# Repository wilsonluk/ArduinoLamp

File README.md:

Arduino Lamp
============
This Arduinio software and PCB are used to control an LED Desk Lamp.

Repository Contents (Needs Cleanup)
-----------------------------------
* **/Code**  - Arduino Code for LED brightness and color control, temperature monitor, and fan control
* **/Mounting**  - 3D Printer Models for mounting hardware
* **/Hardware**  - PCB Files and Parts Lists

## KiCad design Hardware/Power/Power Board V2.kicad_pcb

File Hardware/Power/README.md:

Arduino Lamp - Hardware
============
Hardaware Files (PCB Design, Component Choice / BOM).<br>
PCB / Schematic created using *[KiCad](https://kicad-pcb.org/)*

Folder Contents
---------
* **/BOM**  - Bill of Materials
* **/Datasheets**  - Datasheets for Major Hardaware Components (PMICs, HSF, LEDs)
* **/Libraries**  - KiCad Library Files for Symbols and Footprints
* **/PCB**  - KiCad PCB Files
* **/Resources**  - Other Resources
* **/Schematic**  - KiCad Schematic Files

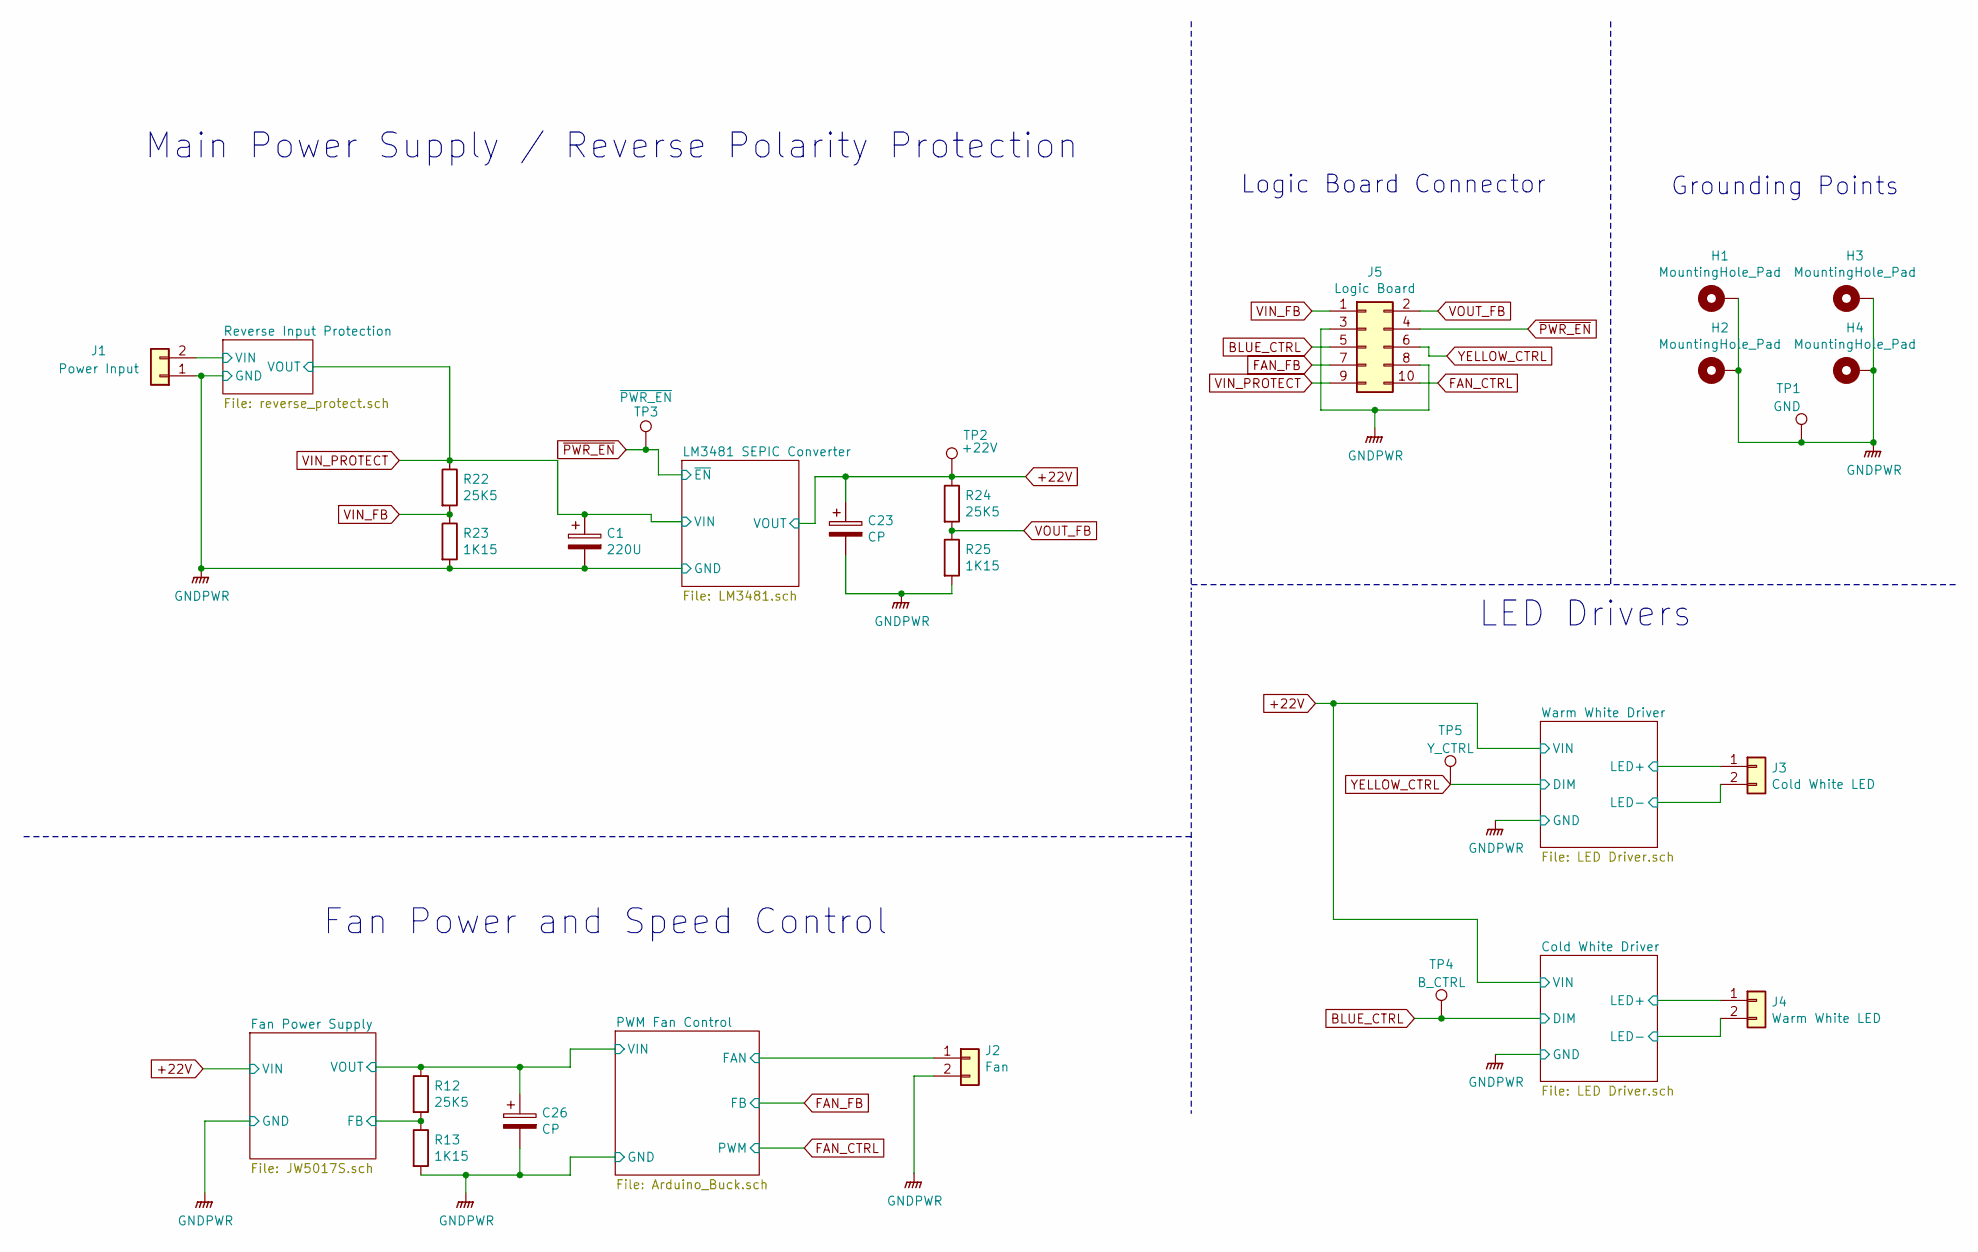
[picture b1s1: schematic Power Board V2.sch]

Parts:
C1: 220U; CP_Radial_D8.0mm_P3.50mm
C23: CP; CP_Radial_D10.0mm_P5.00mm
C26: CP; CP_Radial_D6.3mm_P2.50mm
H1, H2, H3, H4: MountingHole_Pad; MountingHole_3.2mm_M3_Pad_Via
J1: Power Input; JST_XH_B2B-XH-A_1x02_P2.50mm_Vertical
J2: Fan; JST_XH_B2B-XH-A_1x02_P2.50mm_Vertical
J3: Cold White LED; JST_XH_B2B-XH-A_1x02_P2.50mm_Vertical
J4: Warm White LED; JST_XH_B2B-XH-A_1x02_P2.50mm_Vertical
J5: Logic Board; IDC-Header_2x05_P2.54mm_Vertical
R12, R22, R24: 25K5; R_0603_1608Metric_Pad1.05x0.95mm_HandSolder; Manufacturer_Part_Number RS-05K2552FT
R13, R23, R25: 1K15; R_0603_1608Metric_Pad1.05x0.95mm_HandSolder; Manufacturer_Part_Number RS-03K1151FT
TP1: GND; TestPoint_Pad_D1.5mm
TP2: +22V; TestPoint_Pad_D1.5mm
TP3: ~PWR_EN; TestPoint_Pad_D1.5mm
TP4: B_CTRL; TestPoint_Pad_D1.5mm
TP5: Y_CTRL; TestPoint_Pad_D1.5mm

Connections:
+22V: C23.1, R24.1, TP2.1; also elsewhere on the board
/Cold White Driver/LED+: J4.1; also elsewhere on the board
/Cold White Driver/LED-: J4.2; also elsewhere on the board
/Fan Power Supply/FB: R12.2, R13.1; also elsewhere on the board
/PWM Fan Control/FAN: J2.1; also elsewhere on the board
/PWM Fan Control/VIN: C26.1, R12.1; also elsewhere on the board
/Reverse Input Protection/VIN: J1.2; also elsewhere on the board
/Warm White Driver/LED+: J3.1; also elsewhere on the board
/Warm White Driver/LED-: J3.2; also elsewhere on the board
BLUE_CTRL: J5.5, TP4.1; also elsewhere on the board
FAN_CTRL: J5.10; also elsewhere on the board
FAN_FB: J5.7; also elsewhere on the board
GNDPWR: C1.2, C23.2, C26.2, H1.1, H2.1, H3.1, H4.1, J1.1, J2.2, J5.3, J5.8, R13.2, R23.2, R25.2, TP1.1; also elsewhere on the board
VIN_FB: J5.1, R22.2, R23.1
VIN_PROTECT: C1.1, J5.9, R22.1; also elsewhere on the board
VOUT_FB: J5.2, R24.2, R25.1
YELLOW_CTRL: J5.6, TP5.1; also elsewhere on the board
~PWR_EN: J5.4, TP3.1; also elsewhere on the board

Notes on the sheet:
LED Drivers
Grounding Points
Logic Board Connector
Fan Power and Speed Control
Main Power Supply / Reverse Polarity Protection

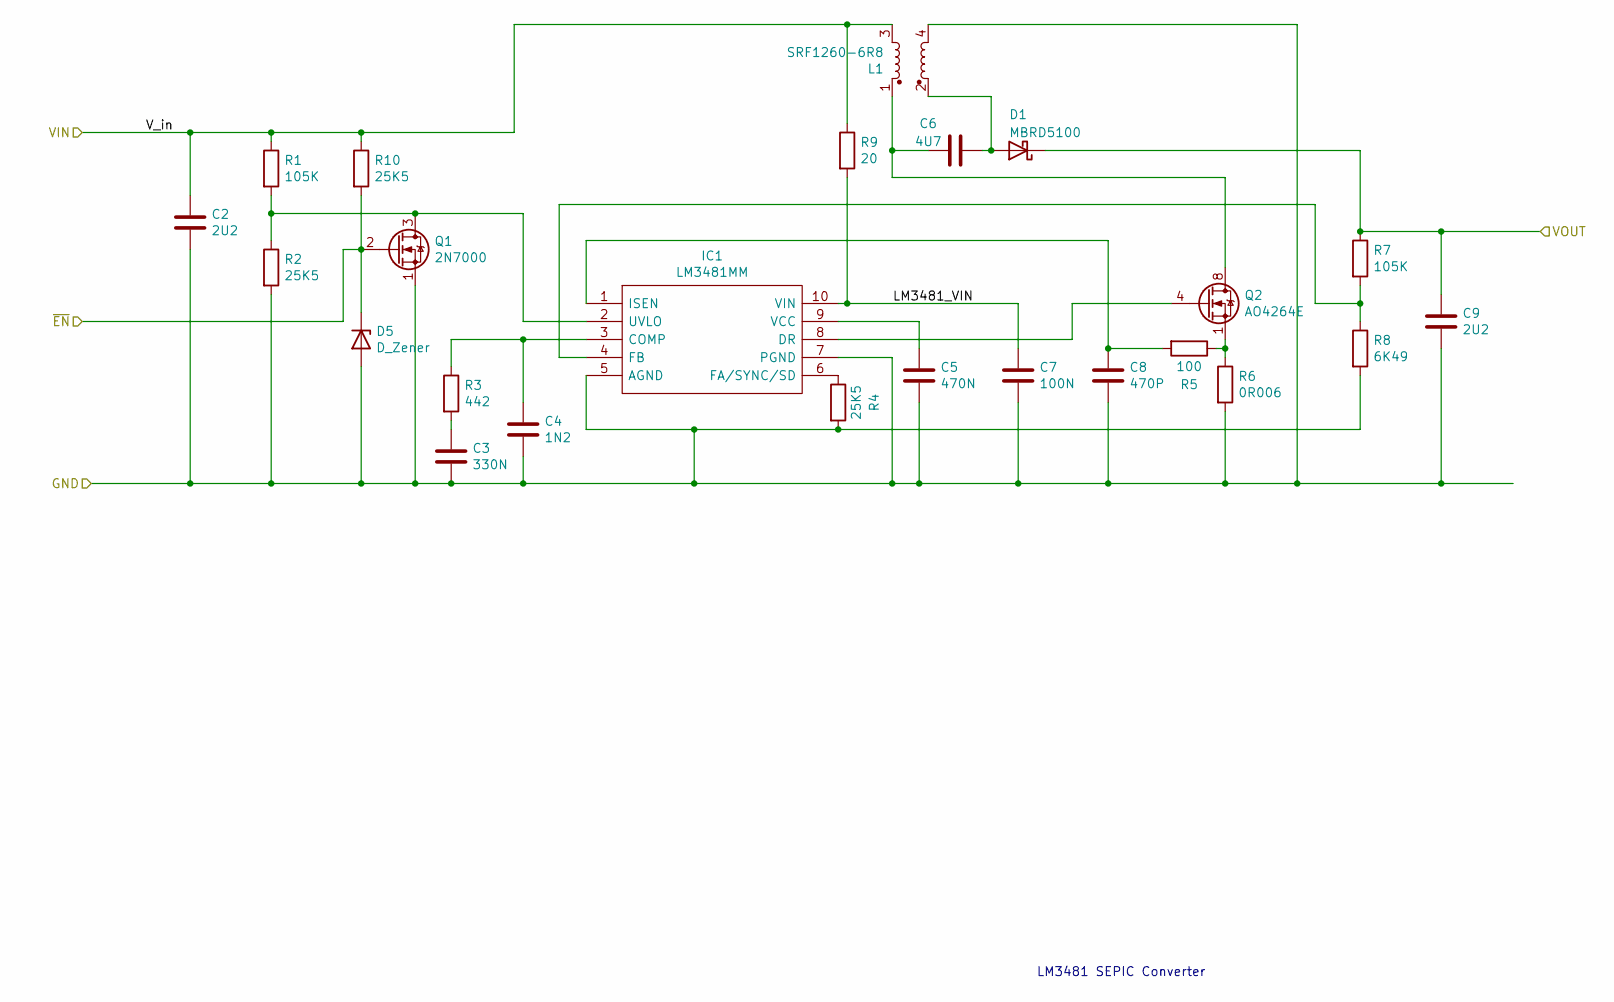
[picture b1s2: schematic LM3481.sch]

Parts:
C2, C9: 2U2; C_0805_2012Metric_Pad1.15x1.40mm_HandSolder; Manufacturer_Part_Number C0805X5R225K500NT
C3: 330N; C_0603_1608Metric_Pad1.05x0.95mm_HandSolder; Manufacturer_Part_Number TCC0603X7R334K500CT
C4: 1N2; C_0603_1608Metric_Pad1.05x0.95mm_HandSolder; Manufacturer_Part_Number C1608C0G1H122JT000N
C5: 470N; C_0603_1608Metric_Pad1.05x0.95mm_HandSolder; Manufacturer_Part_Number 0603B474K100CT
C6: 4U7; C_1206_3216Metric_Pad1.42x1.75mm_HandSolder; Manufacturer_Part_Number GRM31CR71H475KA12L
C7: 100N; C_0603_1608Metric_Pad1.05x0.95mm_HandSolder; Manufacturer_Part_Number CL10B104KB8NNNC
C8: 470P; C_0603_1608Metric_Pad1.05x0.95mm_HandSolder; Manufacturer_Part_Number TCC0603COG471J500CT
D1: MBRD5100; TO-252-2_ConnectedPins
D5: D_Zener; D_SOD-323_HandSoldering; Mouser Part Number MM3Z4V7ST1G
IC1: LM3481MM; VSSOP-10_3x3mm_P0.5mm; Mouser Part Number LM3481MM
L1: SRF1260-6R8; L_Bourns_SRF1260_HandSoldering; Mouser Part Number SRF1260-6R8
Q1: 2N7000; TO-92_Inline; Manufacturer_Part_Number 2N7000
Q2: AO4264E; SO-8_3.9x4.9mm_P1.27mm; Manufacturer_Part_Number AO4264E
R1, R7: 105K; R_0603_1608Metric_Pad1.05x0.95mm_HandSolder; Manufacturer_Part_Number RC0603FR-07105KL
R2, R4, R10: 25K5; R_0603_1608Metric_Pad1.05x0.95mm_HandSolder; Manufacturer_Part_Number RS-05K2552FT
R3: 442; R_0603_1608Metric_Pad1.05x0.95mm_HandSolder; Manufacturer_Part_Number 0603WAF4420T5E
R5: 100; R_0603_1608Metric_Pad1.05x0.95mm_HandSolder; Manufacturer_Part_Number 0603WAJ0101T5E
R6: 0R006; R_1206_3216Metric_Pad1.42x1.75mm_HandSolder; Manufacturer_Part_Number PA1206FRF070R006L
R8: 6K49; R_0603_1608Metric_Pad1.05x0.95mm_HandSolder; Manufacturer_Part_Number RS-03K6491FT
R9: 20; R_0603_1608Metric_Pad1.05x0.95mm_HandSolder; Manufacturer_Part_Number RS-03K19R6FT

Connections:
+22V: C9.1, D1.1 (K), R7.1; also elsewhere on the board
/LM3481 SEPIC Converter/LM3481_VIN: C7.1, IC1.10 (VIN), R9.2
GNDPWR: C2.2, C3.2, C4.2, C5.2, C7.2, C8.2, C9.2, D5.2 (A), IC1.5 (AGND), IC1.7 (PGND), L1.4, Q1.1 (S), R2.2, R4.2, R6.2, R8.2; also elsewhere on the board
unnamed: C3.1, R3.2
unnamed: C4.1, IC1.3 (COMP), R3.1
unnamed: C5.1, IC1.9 (VCC)
unnamed: C6.1, L1.1, Q2.5 (D), Q2.6 (D), Q2.7 (D), Q2.8 (D)
unnamed: C6.2, D1.2 (A), L1.2
unnamed: C8.1, IC1.1 (ISEN), R5.2
unnamed: IC1.2 (UVLO), Q1.3 (D), R1.2, R2.1
unnamed: IC1.4 (FB), R7.2, R8.1
unnamed: IC1.6 (FA/SYNC/SD), R4.1
unnamed: IC1.8 (DR), Q2.4 (G)
unnamed: Q2.1 (S), Q2.2 (S), Q2.3 (S), R5.1, R6.1
VIN_PROTECT: C2.1, L1.3, R1.1, R9.1, R10.1; also elsewhere on the board
~PWR_EN: D5.1 (K), Q1.2 (G), R10.2; also elsewhere on the board

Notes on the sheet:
LM3481 SEPIC Converter

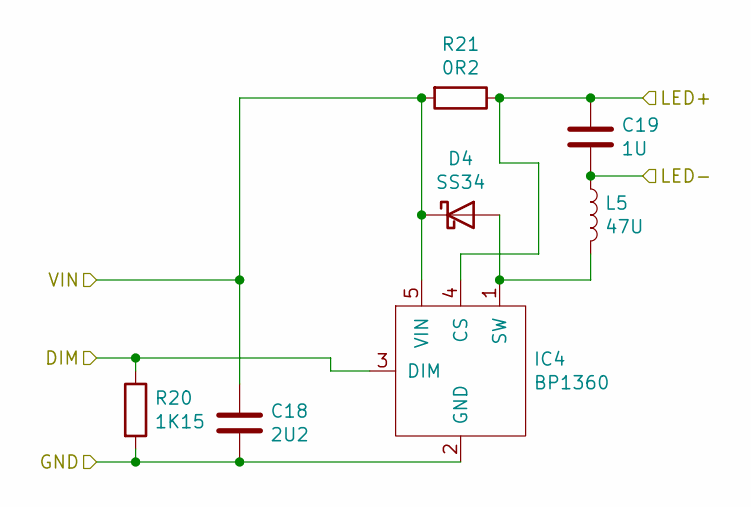
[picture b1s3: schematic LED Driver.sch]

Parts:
C15: 2U2; C_0805_2012Metric_Pad1.15x1.40mm_HandSolder; Manufacturer_Part_Number C0805X5R225K500NT
C16: 1U; C_0805_2012Metric_Pad1.15x1.40mm_HandSolder; Manufacturer_Part_Number TCC0805X7R105K500DTS
D2: SS34; D_SMC_Handsoldering_Shortened
IC2: BP1360; SOT-23-5_HandSoldering; Manufacturer_Part_Number BP1360
L3: 47U; SLD10; Manufacturer_Part_Number SLD10D50S470MTT
R14: 1K15; R_0603_1608Metric_Pad1.05x0.95mm_HandSolder; Manufacturer_Part_Number RS-03K1151FT
R15: 0R2; R_1206_3216Metric_Pad1.42x1.75mm_HandSolder; Manufacturer_Part_Number 1206W3J020LT5E

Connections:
+22V: C15.1, D2.1 (K), IC2.5 (VIN), R15.2; also elsewhere on the board
/Warm White Driver/LED+: C16.1, IC2.4 (CS), R15.1; also elsewhere on the board
/Warm White Driver/LED-: C16.2, L3.1; also elsewhere on the board
GNDPWR: C15.2, IC2.2 (GND), R14.2; also elsewhere on the board
unnamed: D2.2 (A), IC2.1 (SW), L3.2
YELLOW_CTRL: IC2.3 (DIM), R14.1; also elsewhere on the board

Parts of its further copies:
C18: 2U2; C_0805_2012Metric_Pad1.15x1.40mm_HandSolder; Manufacturer_Part_Number C0805X5R225K500NT
C19: 1U; C_0805_2012Metric_Pad1.15x1.40mm_HandSolder; Manufacturer_Part_Number TCC0805X7R105K500DTS
D4: SS34; D_SMC_Handsoldering_Shortened
IC4: BP1360; SOT-23-5_HandSoldering; Manufacturer_Part_Number BP1360
L5: 47U; SLD10; Manufacturer_Part_Number SLD10D50S470MTT
R20: 1K15; R_0603_1608Metric_Pad1.05x0.95mm_HandSolder; Manufacturer_Part_Number RS-03K1151FT
R21: 0R2; R_1206_3216Metric_Pad1.42x1.75mm_HandSolder; Manufacturer_Part_Number 1206W3J020LT5E

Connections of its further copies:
+22V: C18.1, D4.1 (K), IC4.5 (VIN), R21.2; also elsewhere on the board
/Cold White Driver/LED+: C19.1, IC4.4 (CS), R21.1; also elsewhere on the board
/Cold White Driver/LED-: C19.2, L5.1; also elsewhere on the board
BLUE_CTRL: IC4.3 (DIM), R20.1; also elsewhere on the board
GNDPWR: C18.2, IC4.2 (GND), R20.2; also elsewhere on the board
unnamed: D4.2 (A), IC4.1 (SW), L5.2

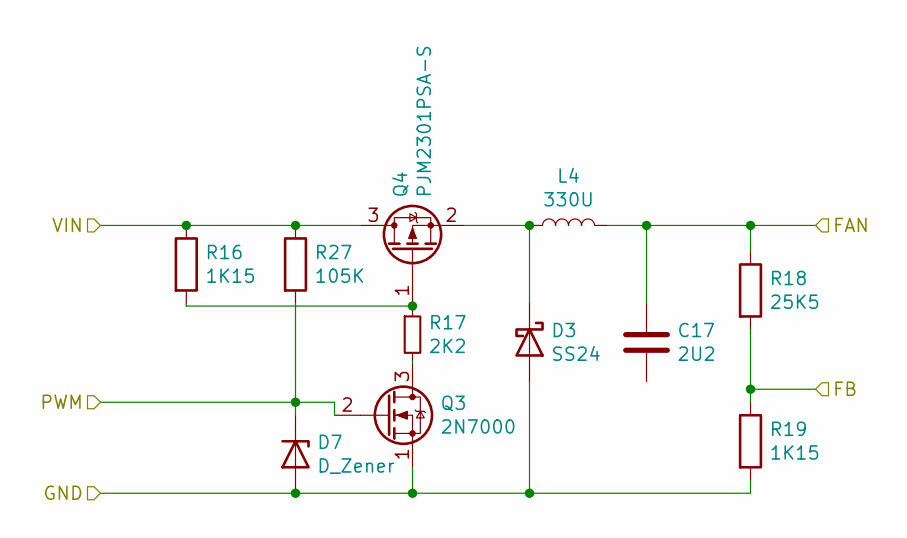
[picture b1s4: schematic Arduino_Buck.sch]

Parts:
C17: 2U2; C_0805_2012Metric_Pad1.15x1.40mm_HandSolder; Manufacturer_Part_Number C0805X5R225K500NT
D3: SS24; D_SMA_Handsoldering_Shortened
D7: D_Zener; D_SOD-323_HandSoldering
L4: 330U; SLD10; Manufacturer_Part_Number SLD10D40S331MTT
Q3: 2N7000; TO-92_Inline; Manufacturer_Part_Number 2N7000
Q4: PJM2301PSA-S; SOT-23; Manufacturer_Part_Number PJM2301PSA-S
R16: 1K15; R_0603_1608Metric_Pad1.05x0.95mm_HandSolder
R17: 2K2; R_0603_1608Metric_Pad1.05x0.95mm_HandSolder
R18: 25K5; R_0603_1608Metric_Pad1.05x0.95mm_HandSolder; Manufacturer_Part_Number RS-05K2552FT
R19: 1K15; R_0603_1608Metric_Pad1.05x0.95mm_HandSolder; Manufacturer_Part_Number RS-03K1151FT
R27: 105K; R_0603_1608Metric_Pad1.05x0.95mm_HandSolder; Manufacturer_Part_Number RC0603FR-07105KL

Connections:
/PWM Fan Control/FAN: C17.1, L4.2, R18.1; also elsewhere on the board
/PWM Fan Control/VIN: Q4.3 (D), R16.1, R27.1; also elsewhere on the board
FAN_CTRL: D7.1 (K), Q3.2 (G), R27.2; also elsewhere on the board
FAN_FB: R18.2, R19.1; also elsewhere on the board
GNDPWR: D3.2 (A), D7.2 (A), Q3.1 (S), R19.2; also elsewhere on the board
unnamed: D3.1 (K), L4.1, Q4.2 (S)
unnamed: Q3.3 (D), R17.2
unnamed: Q4.1 (G), R16.2, R17.1

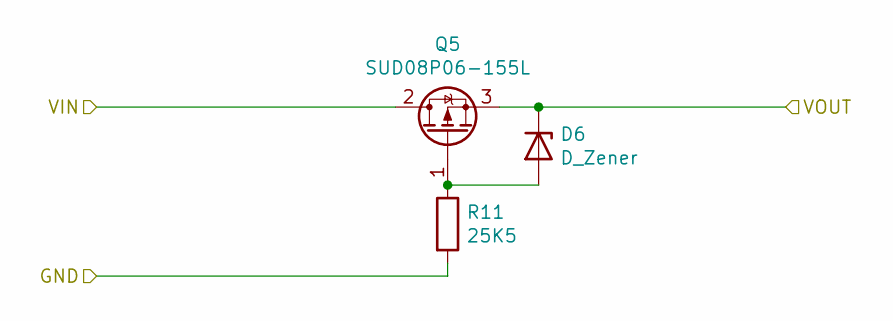
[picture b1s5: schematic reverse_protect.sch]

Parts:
D6: D_Zener; D_SOD-323_HandSoldering
Q5: SUD08P06-155L; TO-252-2
R11: 25K5; R_0603_1608Metric_Pad1.05x0.95mm_HandSolder; Manufacturer_Part_Number RS-05K2552FT

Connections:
/Reverse Input Protection/VIN: Q5.2 (D); also elsewhere on the board
GNDPWR: R11.2; also elsewhere on the board
unnamed: D6.2 (A), Q5.1 (G), R11.1
VIN_PROTECT: D6.1 (K), Q5.3 (S); also elsewhere on the board

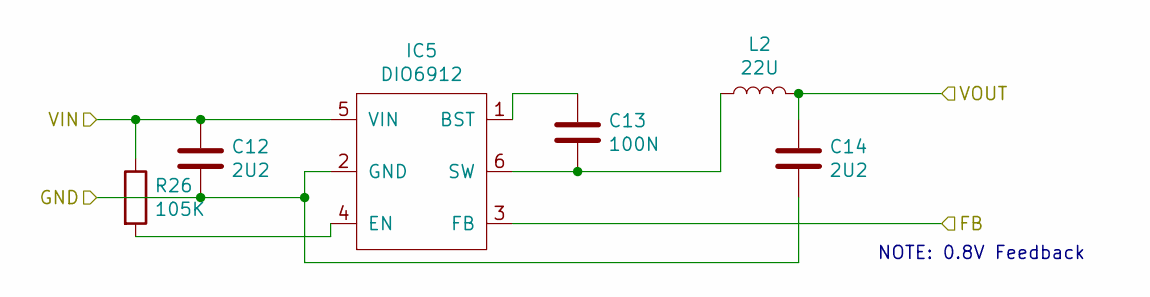
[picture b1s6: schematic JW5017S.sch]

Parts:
C20, C22: 2U2; C_0805_2012Metric_Pad1.15x1.40mm_HandSolder; Manufacturer_Part_Number C0805X5R225K500NT
C21: 100N; C_0603_1608Metric_Pad1.05x0.95mm_HandSolder; Manufacturer_Part_Number CL10B104KB8NNNC
IC3: DIO6912; SOT-23-6_Handsoldering; Manufacturer_Part_Number DIO6912
L6: 22U; YT0630; Manufacturer_Part_Number YT0630-220M
R26: 105K; R_0603_1608Metric_Pad1.05x0.95mm_HandSolder; Manufacturer_Part_Number RC0603FR-07105KL

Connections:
+22V: R26.1; also elsewhere on the board
unnamed 31: R26.2; also elsewhere on the board

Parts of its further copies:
C12, C14: 2U2; C_0805_2012Metric_Pad1.15x1.40mm_HandSolder; Manufacturer_Part_Number C0805X5R225K500NT
C13: 100N; C_0603_1608Metric_Pad1.05x0.95mm_HandSolder; Manufacturer_Part_Number CL10B104KB8NNNC
IC5: DIO6912; SOT-23-6_Handsoldering; Manufacturer_Part_Number DIO6912
L2: 22U; YT0630; Manufacturer_Part_Number YT0630-220M

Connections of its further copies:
+22V: C12.1, IC5.5 (VIN); also elsewhere on the board
/Fan Power Supply/FB: IC5.3 (FB); also elsewhere on the board
/PWM Fan Control/VIN: C14.1, L2.2; also elsewhere on the board
GNDPWR: C12.2, C14.2, IC5.2 (GND); also elsewhere on the board
unnamed: C13.1, IC5.1 (BST)
unnamed: C13.2, IC5.6 (SW), L2.1
unnamed 31: IC5.4 (EN); also elsewhere on the board

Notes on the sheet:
NOTE: 0.8V Feedback

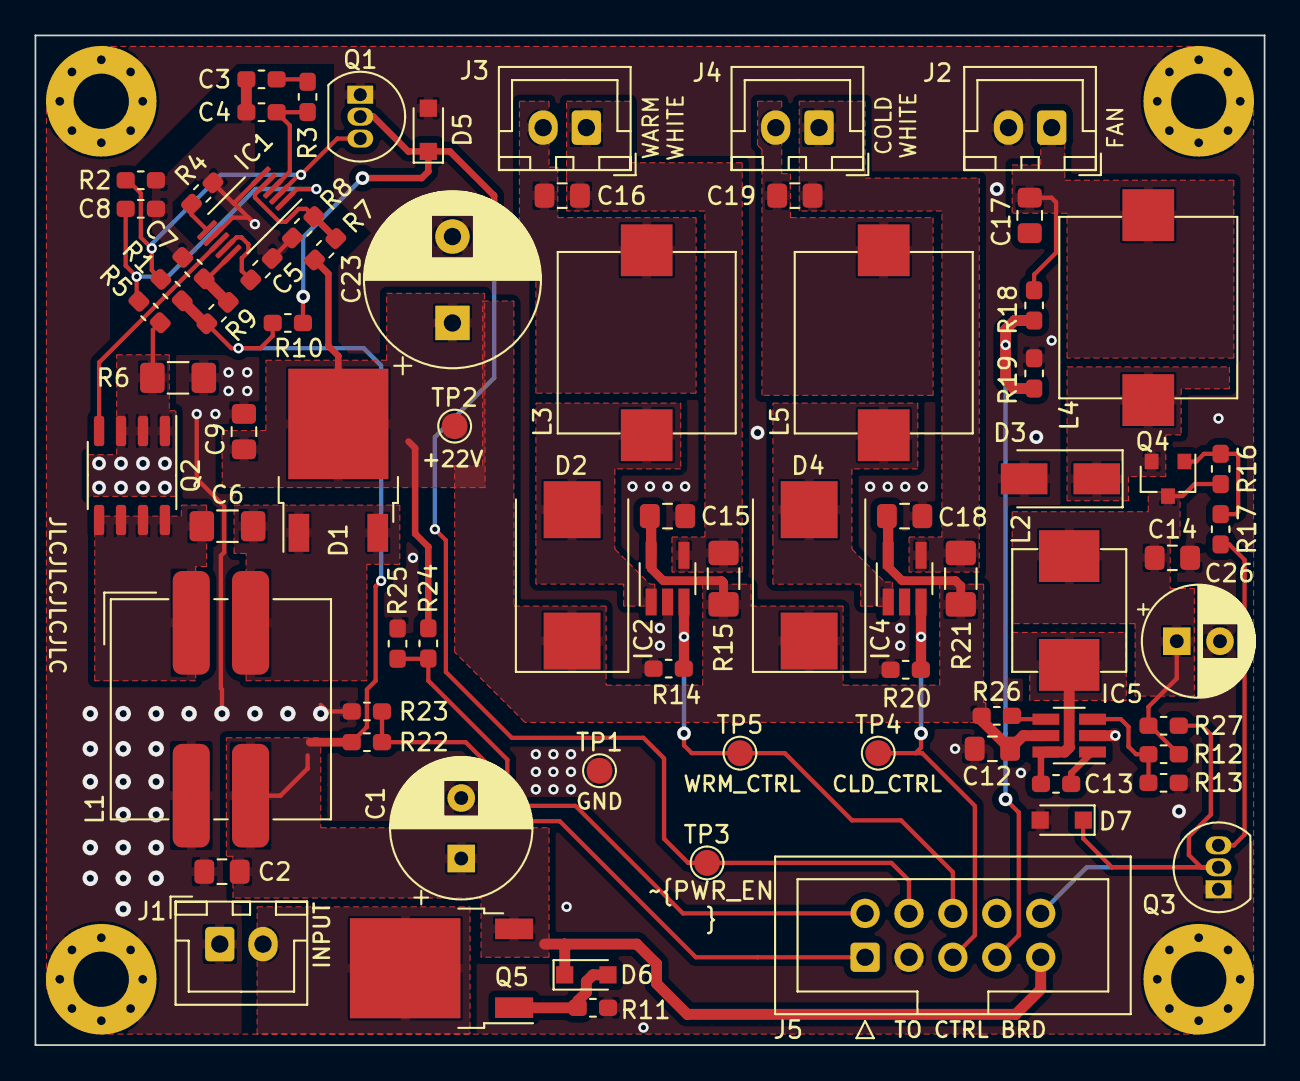
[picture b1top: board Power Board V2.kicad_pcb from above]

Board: 2 copper layers, 71.1 x 58.4 mm, 81 parts (0 on the bottom side), 39 nets.

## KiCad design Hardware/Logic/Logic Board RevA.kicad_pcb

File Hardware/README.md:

Arduino Lamp Hardware
=====================
PCB Files and Libraries for the ArduinoLamp

Lastest PCB revisions created using *[KiCad](https://kicad-pcb.org/)*.

Power Board V1 created using *[EAGLE](https://www.autodesk.com/products/eagle/overview/)* (see ZIP archive).

Folder Contents
-----------------------------------
* **/BOM**  - Bill of Materials of the PCBs
* **/Datasheets**  - Datasheets for relevant ICs and other components
* **/Libraries**  - KiCad Footprint and Schematic Libraries
* **/Logic** - KiCad schematic and layout files for Logic Board
* **/Power** - KiCad schematic and layout files for Power Board
* **/Resources** - Misc. Resources for Boards

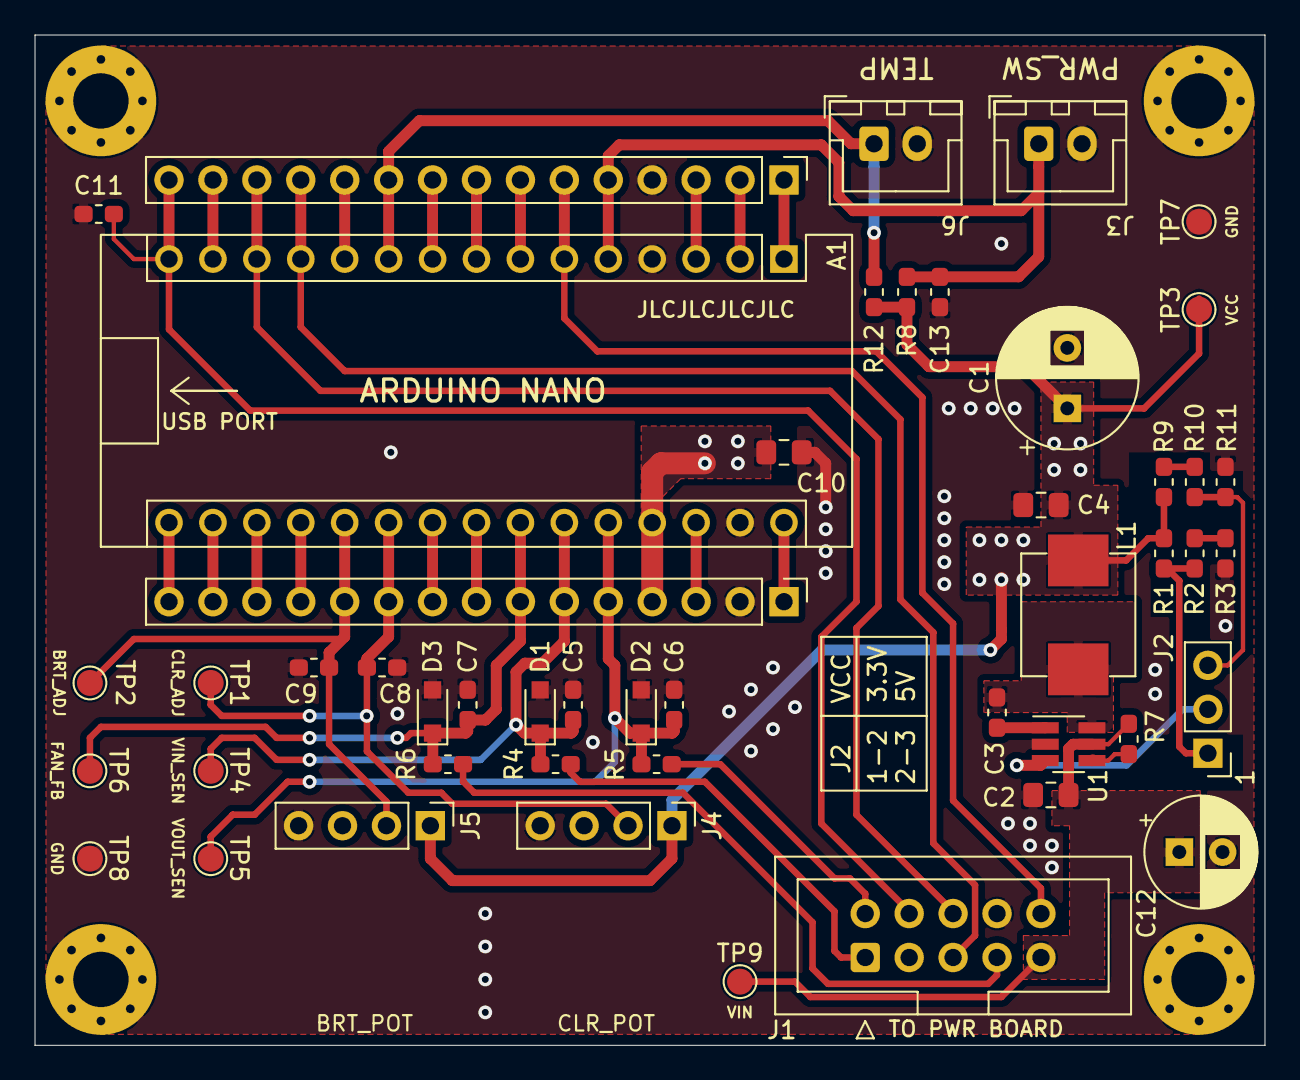
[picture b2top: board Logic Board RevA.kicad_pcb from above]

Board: 2 copper layers, 71.1 x 58.4 mm, 50 parts (0 on the bottom side), 25 nets.

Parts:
A1: Arduino_Nano_v3.x; Arduino_Nano_3D
C1: CP; CP_Radial_D8.0mm_P3.50mm
C2, C4, C10: 2U2; C_0805_2012Metric_Pad1.15x1.40mm_HandSolder
C3: 100N; C_0603_1608Metric_Pad1.05x0.95mm_HandSolder
C5, C6, C7: 1N2; R_0603_1608Metric_Pad1.05x0.95mm_HandSolder
C8, C9, C13: 100N; R_0603_1608Metric_Pad1.05x0.95mm_HandSolder
C11: 470P; C_0603_1608Metric_Pad1.05x0.95mm_HandSolder
C12: 47U; CP_Radial_D6.3mm_P2.50mm
D1, D2, D3: D_Zener; D_SOD-323_HandSoldering
H1, H2, H3, H4: MountingHole_Pad; MountingHole_3.2mm_M3_Pad_Via
J1: Conn_02x05_Counter_Clockwise; IDC-Header_2x05_P2.54mm_Vertical
J2: Conn_01x03_Male; PinHeader_1x03_P2.54mm_Vertical
J3, J6: Conn_01x02; JST_XH_B2B-XH-A_1x02_P2.50mm_Vertical
J4, J5: Conn_01x04; PinHeader_1x04_P2.54mm_Vertical
L1: 22U; YT0630
R1: 6K49; R_0603_1608Metric_Pad1.05x0.95mm_HandSolder
R2: 1K; R_0603_1608Metric_Pad1.05x0.95mm_HandSolder
R3: 442; R_0603_1608Metric_Pad1.05x0.95mm_HandSolder
R4, R5, R6, R9: 8K45; R_0603_1608Metric_Pad1.05x0.95mm_HandSolder
R7: 105K; R_0603_1608Metric_Pad1.05x0.95mm_HandSolder
R8, R12: 2K2; R_0603_1608Metric_Pad1.05x0.95mm_HandSolder
R10: 100R; R_0603_1608Metric_Pad1.05x0.95mm_HandSolder
R11: 1K15; R_0603_1608Metric_Pad1.05x0.95mm_HandSolder
TP1, TP2, TP3, TP4, TP5, TP6, TP7, TP8, TP9: TestPoint; TestPoint_Pad_D1.5mm
U1: DIO6912; SOT-23-6_Handsoldering

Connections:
BLUE_CTRL: A1.12, J1.5
BRT_ADJ: A1.20, C9.1, J5.2, TP2.1
CLR_ADJ: A1.21, C8.1, J4.2, TP1.1
FAN_CTRL: A1.6, J1.10
FAN_FB: J1.7, R6.2
FAN_FB_P: A1.24, C7.1, D3.1, R6.1, TP6.1
GNDPWR: A1.4, A1.29, C1.2, C2.2, C4.2, C5.2, C6.2, C7.2, C8.2, C9.2, C10.2, C11.2, C12.2, C13.2, D1.2, D2.2, D3.2, H1.1, H2.1, H3.1, H4.1, J1.3, J1.8, J3.2, J4.4, J5.4, J6.2, R3.1, R11.1, TP7.1, TP8.1, U1.2
unnamed: C3.1, U1.1
unnamed: C3.2, L1.1, U1.6
unnamed: J2.1, R1.2, R2.1
unnamed: J2.3, R10.2, R11.2
unnamed: R2.2, R3.2
unnamed: R7.2, U1.4
unnamed: R9.2, R10.1
PWR_SW: A1.5, C13.1, J3.1, R8.2
TEMP_SENSE: A1.10, J6.1, R12.2
VCC: A1.27, C1.1, C4.1, C10.1, J4.1, J5.1, L1.2, R1.1, R8.1, R9.1, R12.1, TP3.1
VCC_FB: J2.2, U1.3
VIN_PROTECT: C2.1, C12.1, J1.9, R7.1, TP9.1, U1.5
VIN_SENSE: J1.1, R4.2
VIN_SENSE_P: A1.25, C5.1, D1.1, R4.1, TP4.1
VOUT_SENSE: J1.2, R5.2
VOUT_SENSE_P: A1.26, C6.1, D2.1, R5.1, TP5.1
YELLOW_CTRL: A1.13, J1.6
~PWR_EN: A1.15, C11.1, J1.4

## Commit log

2020-06-20 Inital Commit
2020-07-10 Voltage Monitoring
2020-07-11 Maintenance
2020-07-14 LED Driver IP
2020-07-15 Completed LED Shared Variables
2020-07-25 Added Over Temperature Protection Shutdown
2020-07-31 Fixed Task Priorities
2020-07-31 Changed LED Brightness Ramp Profile
2020-08-13 Moved ADC source to decrease sensor noise
2020-10-13 Added Readme
2020-10-19 Added KiCad Project
2020-10-19 Cleanup
2020-10-19 Cleanup, Added Datasheets and Readmes
2020-10-19 Fixed gitignore
2020-10-19 Fixed .gitignore
2020-11-08 Added Power Board Rev. B
2020-11-10 KiCad Cleanup
2020-11-10 Initial Logic Board Commit
2020-11-10 KiCad FIle Cleanup
2020-11-11 Included Legacy V1 PCBs
2020-11-14 Moved MCU Power Supply to Logic Board
2020-11-20 Removed Logic Board PSU from Power Board
2020-11-20 Logic Board PCB Design
2020-11-20 Added Readme for Hardware Folder
2020-11-20 Cleaned Up Readmes for Hardware Folders
2020-11-21 Cleaned Up gitignore
2020-11-23 Inital Interrupt Test
2020-12-07 Fixed Power Board Errata
2020-12-09 Revised PCB Bracket for Rev. B/B1 Power Boards
2020-12-10 Edited PlatformIO config to support colors
2020-12-10 Power On Self Test Prototype
2020-12-16 (IP) Software Stack Revamp
2021-01-08 Moved to MiniCore Bootloader
2021-01-08 Message Printing Moved to printf
